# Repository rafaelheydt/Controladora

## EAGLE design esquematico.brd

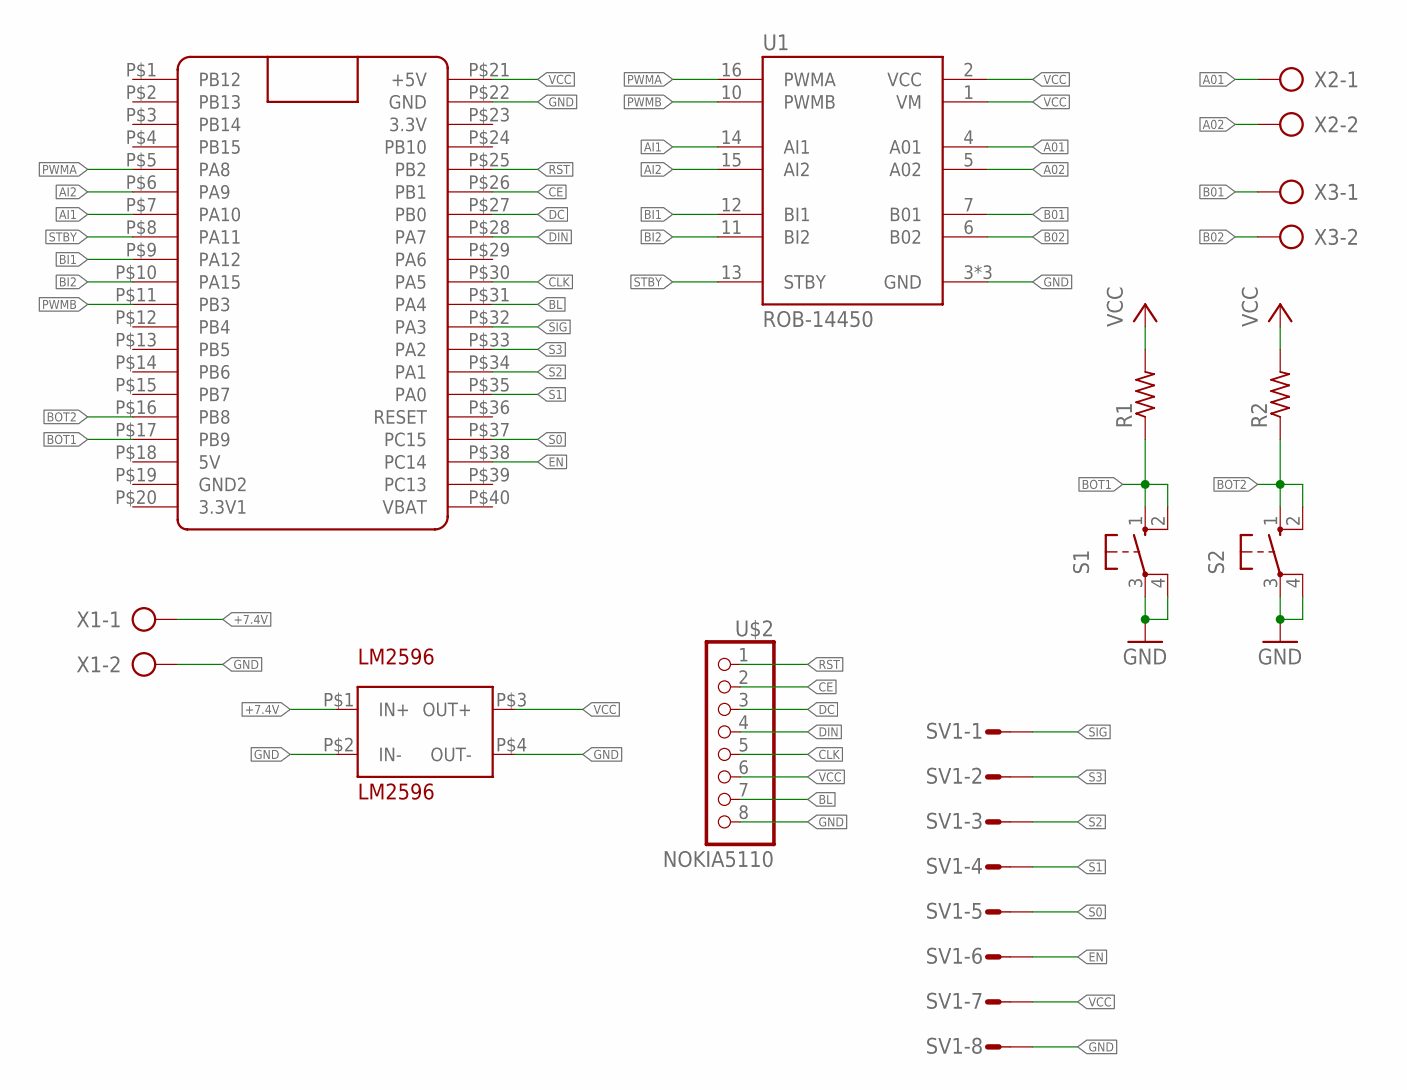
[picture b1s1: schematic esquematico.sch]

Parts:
R1, R2: R-US_0204/7; 0204/7
S1, S2: 10-XX; B3F-10XX
SV1: S08P
U1: ROB-14450; MODULE_ROB-14450
U$1: BLUE_PILL
U$2: NOKIA5110; 1X08
U$3: LM2596
X1, X2, X3: AK300/2

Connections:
+7.4V: U$3.P$1 (IN+), X1.1
A01: U1.4 (A01), X2.1
A02: U1.5 (A02), X2.2
AI1: U1.14 (AI1), U$1.P$7 (PA10)
AI2: U1.15 (AI2), U$1.P$6 (PA9)
B01: U1.7 (B01), X3.1
B02: U1.6 (B02), X3.2
BI1: U1.12 (BI1), U$1.P$9 (PA12)
BI2: U1.11 (BI2), U$1.P$10 (PA15)
BL: U$1.P$31 (PA4), U$2.7
BOT1: R1.1, S1.1 (S), S1.2 (S1), U$1.P$17 (PB9)
BOT2: R2.1, S2.1 (S), S2.2 (S1), U$1.P$16 (PB8)
CE: U$1.P$26 (PB1), U$2.2
CLK: U$1.P$30 (PA5), U$2.5
DC: U$1.P$27 (PB0), U$2.3
DIN: U$1.P$28 (PA7), U$2.4
EN: SV1.6, U$1.P$38 (PC14)
GND: S1.3, S1.4 (P1), S2.3, S2.4 (P1), SV1.8, U1.3 (GND), U1.8 (GND), U1.9 (GND), U$1.P$22 (GND), U$2.8, U$3.P$2 (IN-), U$3.P$4 (OUT-), X1.2
PWMA: U1.16 (PWMA), U$1.P$5 (PA8)
PWMB: U1.10 (PWMB), U$1.P$11 (PB3)
RST: U$1.P$25 (PB2), U$2.1
S0: SV1.5, U$1.P$37 (PC15)
S1: SV1.4, U$1.P$35 (PA0)
S2: SV1.3, U$1.P$34 (PA1)
S3: SV1.2, U$1.P$33 (PA2)
SIG: SV1.1, U$1.P$32 (PA3)
STBY: U1.13 (STBY), U$1.P$8 (PA11)
VCC: R1.2, R2.2, SV1.7, U1.1 (VM), U1.2 (VCC), U$1.P$21 (+5V), U$2.6, U$3.P$3 (OUT+)

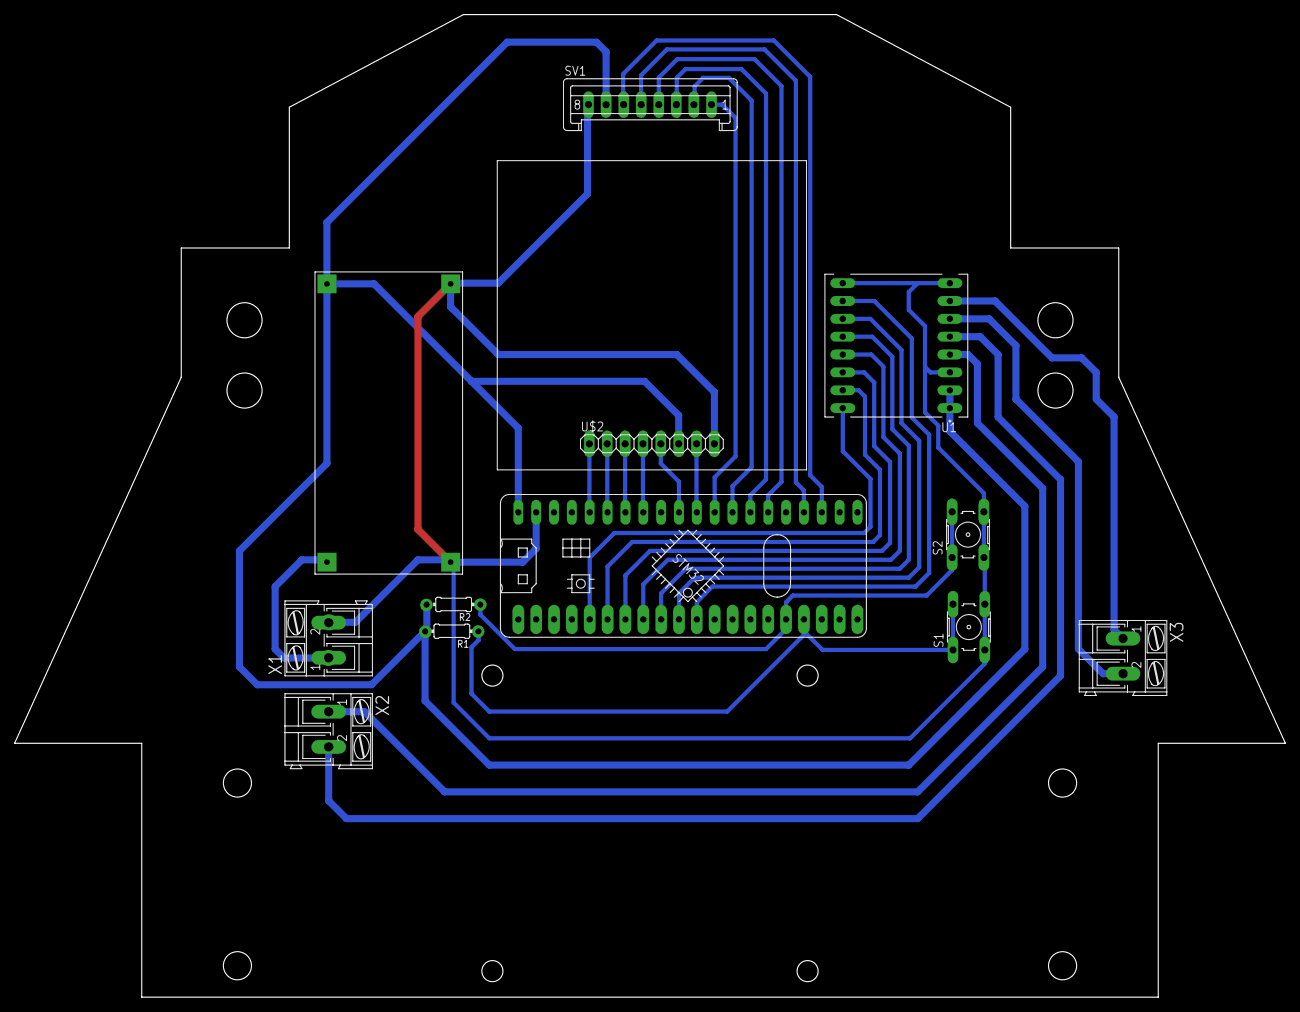
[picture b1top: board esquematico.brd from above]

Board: 2 copper layers, 180.8 x 139.8 mm, 12 parts (0 on the bottom side), 28 nets.

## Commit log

2023-08-08 Initial_Commit
2023-08-08 Esquematico
    Adição do esquematico
2023-08-08 adicionei um led
2023-08-08 08/08 - 17:26
    Adição de bibliotecas e esquemáticos.
2023-08-09 Design PCB
    Criação formato da PCB
2023-08-09 Adição do furo na PCB
2023-08-31 change esquematico
2023-09-01 Create DRV8833 Lib
2023-09-01 Att lib
2023-09-06 Atualização Pinos STM32 e Lib
2023-09-06 Atualização Drive
2023-09-07 Design Board.
2023-09-07 Trilhas V1
2023-09-07 Trilhas V2
2023-09-15 Trilhas V3
2023-09-19 Atualização furos PCB/Trilhas
2023-10-04 Trilhas V4
2023-10-04 Trilhas V5
